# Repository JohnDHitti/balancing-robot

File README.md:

# balancing-robot
Source code for a balancing robot project conducted at Fort Lewis College. The balancing robot was a project where an atmega328p was used as a PID controller on a custom PCB to control two stepper motors to balance a vertical tower shaped robot. This robot also featured a wireless remote control option. (Pre-freeRTOS)

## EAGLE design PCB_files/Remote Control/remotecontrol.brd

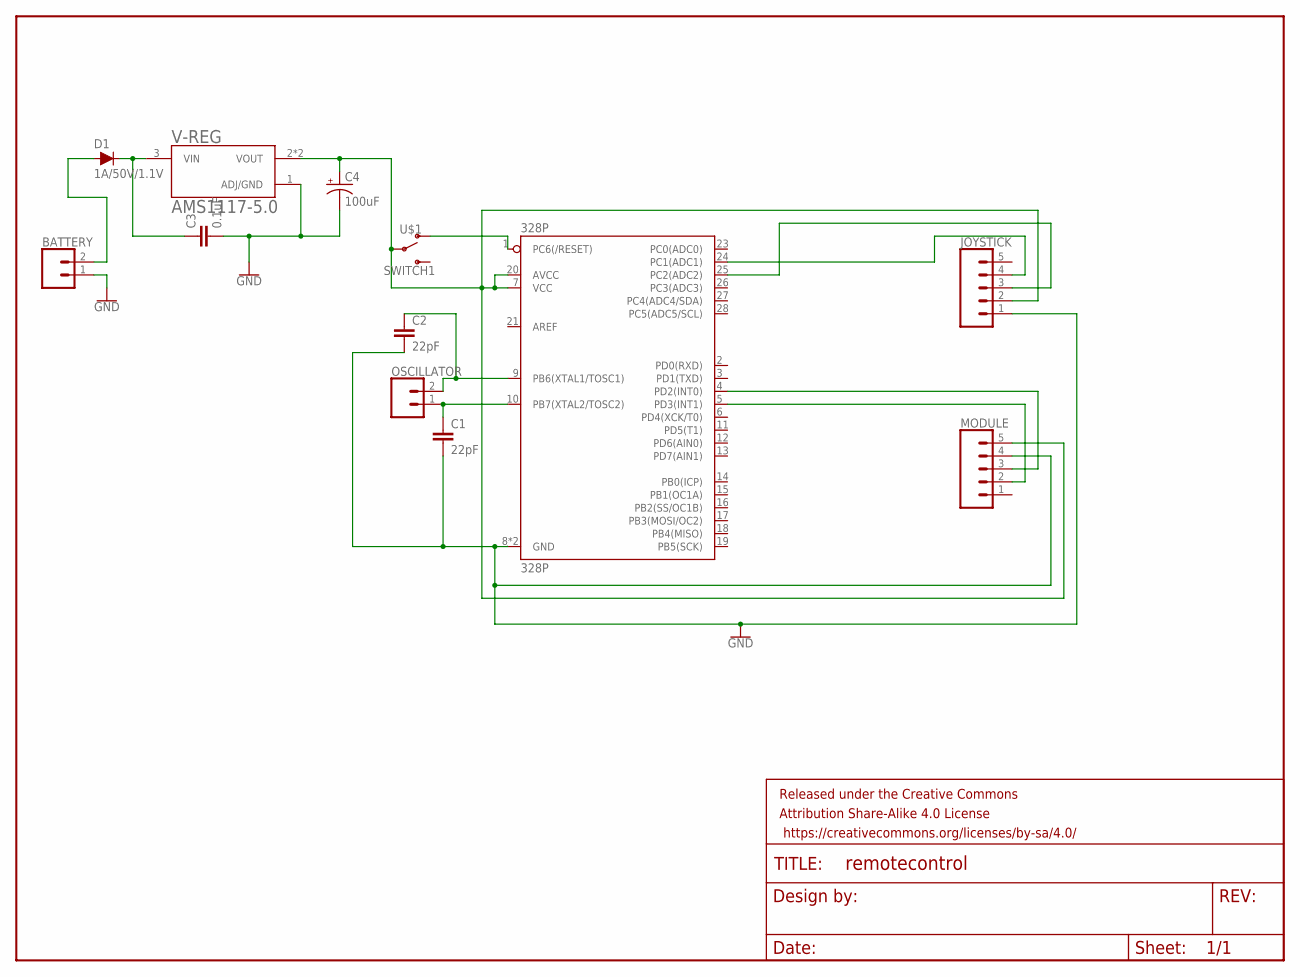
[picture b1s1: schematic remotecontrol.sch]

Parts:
328P: 328P; DIP28
BATTERY: CONN_02; 1X02
C1, C2: 22pF; 0603
C3: 0.1uF; 0603
C4: 100uF; NIC_10X10.5_CAP
D1: 1A/50V/1.1V; DIODE-1N4001
FRAME1: FRAME-LETTER; CREATIVE_COMMONS
JOYSTICK: CONN_05; 1X05
MODULE: CONN_05; 1X05
OSCILLATOR: CONN_02; 1X02
U$1: SWITCH1
V-REG: AMS1117-5.0; SOT229P700X180-4N

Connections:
GND: 328P.8 (GND), 328P.22 (GND), BATTERY.1, C1.2, C2.2, C3.2, C4.-, JOYSTICK.1, MODULE.4, V-REG.1 (ADJ/GND)
JOYSTICK: 328P.24 (PC1(ADC1)), JOYSTICK.4
unnamed: 328P.5 (PD3(INT1)), MODULE.2
unnamed: 328P.4 (PD2(INT0)), MODULE.3
unnamed: BATTERY.2, D1.A
unnamed: 328P.25 (PC2(ADC2)), JOYSTICK.3
unnamed: C3.1, D1.C, V-REG.3 (VIN)
unnamed: 328P.10 (PB7(XTAL2/TOSC2)), C1.1, OSCILLATOR.1
unnamed: 328P.9 (PB6(XTAL1/TOSC1)), C2.1, OSCILLATOR.2
unnamed: 328P.1 (PC6(/RESET)), U$1.P$3 (O)
unnamed: 328P.7 (VCC), 328P.20 (AVCC), C4.+, JOYSTICK.2, MODULE.5, U$1.P$2, V-REG.2 (VOUT), V-REG.4 (VOUT)

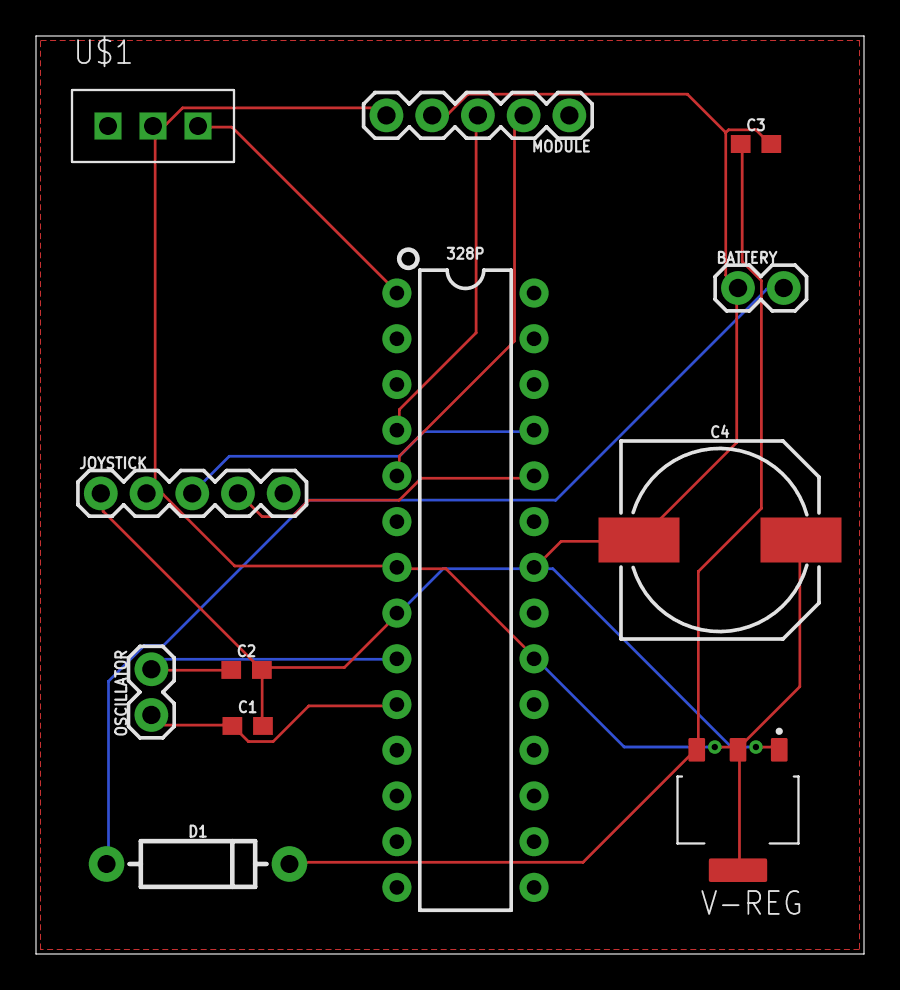
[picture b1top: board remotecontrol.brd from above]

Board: 2 copper layers, 46.0 x 51.0 mm, 13 parts (0 on the bottom side), 11 nets.

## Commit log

2022-04-07 Rename motorexample.ino to motor_driver_test.ino
2022-04-07 Rename Balancing_robot_Jh.ino to Main_Balancing_Robot.ino

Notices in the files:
parts and their libraries:
SparkFun-Capacitors: Licensing: Creative Commons ShareAlike 4.0 International - https://creativecommons.org/licenses/by-sa/4.0
SparkFun-Aesthetics: Released under the Creative Commons Attribution Share-Alike 4.0 License
SparkFun-Aesthetics: https://creativecommons.org/licenses/by-sa/4.0
